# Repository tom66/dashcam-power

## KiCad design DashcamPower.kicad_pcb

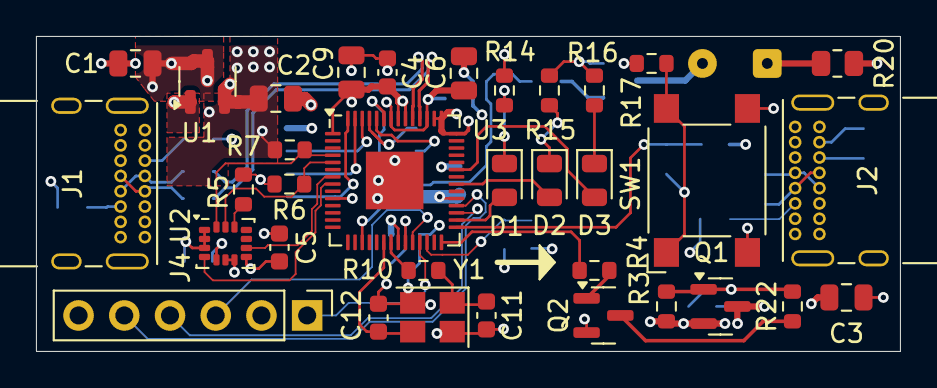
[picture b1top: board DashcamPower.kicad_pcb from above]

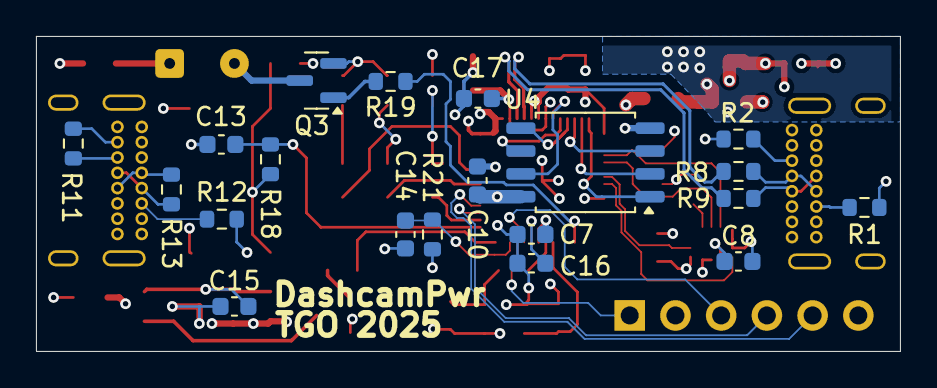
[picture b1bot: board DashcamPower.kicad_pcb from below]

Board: 6 copper layers, 48.0 x 17.5 mm, 55 parts (20 on the bottom side), 50 nets.

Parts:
C1, C3: 4.7u 25V; C_0805_2012Metric
C2, C6, C9: 1u 50V; C_0805_2012Metric
C4, C5, C7, C8, C10, C13, C14, C15, C16, C17: 100n; C_0603_1608Metric
C11, C12: 15p; C_0603_1608Metric
D1: Green 0805; LED_0805_2012Metric
D2: Red 0805; LED_0805_2012Metric
D3: Yellow 0805; LED_0805_2012Metric
J1, J2: USB_C_Receptacle_USB2.0_16P; USB_C_Receptacle_GCT_USB4085
J4: Conn_01x06; PinHeader_1x06_P2.54mm_Vertical
LS1: Speaker_Crystal; SolderWire-0.1sqmm_1x02_P3.6mm_D0.4mm_OD1mm
Q1: IRLML6402; SOT-23
Q2, Q3: MMBT5551L; SOT-23
R1, R2, R3, R4, R5, R6, R7, R11, R12, R17, R19, R21: 5.1k; R_0603_1608Metric
R8, R9: 27R; R_0603_1608Metric
R10: 1k; R_0603_1608Metric
R13: NF; R_0603_1608Metric
R14, R15, R16, R18, R22: 270R; R_0603_1608Metric
R20: 0R; R_0805_2012Metric
SW1: B3FS-1000P; SW_SPST_Omron_B3FS-100xP
U1: XC6206P332MR-G; SOT-23-3
U2: LSM6DS3; LGA-14_3x2.5mm_P0.5mm_LayoutBorder3x4y
U3: RP2040; QFN-56-1EP_7x7mm_P0.4mm_EP3.2x3.2mm
U4: W25Q128JVS; SOIC-8_5.3x5.3mm_P1.27mm
Y1: X322512MSB4SI; Crystal_SMD_Abracon_ABM8AIG-4Pin_3.2x2.5mm

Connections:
+3.3V: C2.1, C4.1, C5.1, C7.1, C8.1, C9.1, C10.1, J4.6, R5.1, R6.1, R7.1, R17.1, R21.1, U1.2 (VO), U2.5 (VDDIO), U2.8 (VDD), U3.1 (IOVDD), U3.10 (IOVDD), U3.22 (IOVDD), U3.33 (IOVDD), U3.42 (IOVDD), U3.43 (ADC_AVDD), U3.44 (VREG_IN), U3.48 (USB_VDD), U3.49 (IOVDD), U4.8 (VCC)
+5V: C1.1, J1.A4 (VBUS), J1.A9 (VBUS), J1.B4 (VBUS), J1.B9 (VBUS), Q1.2 (S), R3.1, R20.1, U1.3 (VI)
/BTN: C13.1, R18.2, U3.29 (GPIO18)
/BUZZER: R19.1, U3.17 (GPIO14)
/I2C_SCL: R6.2, U2.13 (SCL), U3.5 (GPIO3)
/I2C_SDA: R7.2, U2.14 (SDA), U3.4 (GPIO2)
/IMU_INT1: U2.4 (INT1), U3.8 (GPIO6)
/IMU_INT2: U2.9 (INT2), U3.7 (GPIO5)
/LED_G: D1.2 (A), U3.30 (GPIO19)
/LED_R: D2.2 (A), U3.35 (GPIO23)
/LED_Y: D3.2 (A), U3.37 (GPIO25)
/QSPI_CLK: U3.52 (QSPI_SCLK), U4.6 (CLK)
/QSPI_SD0: U3.53 (QSPI_SD0), U4.5 (DI/IO_{0})
/QSPI_SD1: U3.55 (QSPI_SD1), U4.2 (DO/IO_{1})
/QSPI_SD2: U3.54 (QSPI_SD2), U4.3 (~WP/IO_{2})
/QSPI_SD3: U3.51 (QSPI_SD3), U4.7 (~HOLD/~RESET/IO_{3})
/QSPI_SS: U3.56 (QSPI_SS), U4.1 (~CS)
/SWC: J4.3, U3.24 (SWCLK)
/SWD: J4.1, U3.25 (SWD)
/URX: J4.5, U3.32 (GPIO21)
/USB_D_N: J1.A7 (D-), J1.B7 (D-), R9.2
/USB_D_P: J1.A6 (D+), J1.B6 (D+), R8.1
/USB_OUT_ON: R4.1, U3.28 (GPIO17)
/USB_RES_D_N: R8.2, U3.47 (USB_DP)
/USB_RES_D_P: R9.1, U3.46 (USB_DM)
/USB_VOUT: C3.1, C15.1, J2.A4 (VBUS), J2.A9 (VBUS), J2.B4 (VBUS), J2.B9 (VBUS), Q1.3 (D), R11.1, R12.1
/UTX: J4.4, U3.31 (GPIO20)
/VCORE: C6.1, C16.1, C17.1, U3.23 (DVDD), U3.45 (VREG_VOUT), U3.50 (DVDD)
GND: C1.2, C2.2, C3.2, C4.2, C5.2, C6.2, C7.2, C8.2, C9.2, C10.2, C11.2, C12.2, C13.2, C14.2, C16.2, C17.2, J1.A1 (GND), J1.A12 (GND), J1.B1 (GND), J1.B12 (GND), J1.S1 (SHIELD), J2.A1 (GND), J2.A12 (GND), J2.B1 (GND), J2.B12 (GND), J2.S1 (SHIELD), J4.2, Q2.2 (E), Q3.2 (E), R1.2, R2.2, R14.2, R15.2, R16.2, SW1.2, U1.1 (GND), U2.1 (SDO/SA0), U2.2 (SDX), U2.3 (SCX), U2.6 (GND), U2.7 (GND), U3.57 (GND), U4.4 (GND), Y1.2, Y1.4
unnamed: C11.1, R10.1, Y1.1
unnamed: D1.1 (K), R14.1
unnamed: D2.1 (K), R15.1
unnamed: D3.1 (K), R16.1
unnamed: J1.A5 (CC1), R2.1
unnamed: J1.B5 (CC2), R1.1
unnamed: J2.A5 (CC1), R12.2
unnamed: J2.B5 (CC2), R11.2
unnamed: J2.A6 (D+), J2.B6 (D+), R13.2
unnamed: J2.A7 (D-), J2.B7 (D-), R13.1
unnamed: LS1.1, R20.2
unnamed: C15.2, Q1.1 (G), R3.2, R22.2
unnamed: Q2.1 (B), R4.2
unnamed: Q2.3 (C), R22.1
unnamed: Q3.1 (B), R19.2
unnamed: LS1.2, Q3.3 (C)
unnamed: R17.2, R18.1, SW1.1
unnamed: R5.2, U2.12 (CS)
unnamed: C14.1, R21.2, U3.26 (RUN)
unnamed: C12.1, U3.20 (XIN), Y1.3
unnamed: R10.2, U3.21 (XOUT)

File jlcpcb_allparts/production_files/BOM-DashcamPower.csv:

Comment,Designator,Footprint,LCSC,Quantity
0R,R20,R_0805_2012Metric,C17477,1
100n,"C10,C13,C14,C15,C16,C17,C4,C5,C7,C8",C_0603_1608Metric,C14663,10
15p,"C11,C12",C_0603_1608Metric,C1644,2
1k,R10,R_0603_1608Metric,C21190,1
1u 50V,"C2,C6,C9",C_0805_2012Metric,C28323,3
270R,"R14,R15,R16,R18,R22",R_0603_1608Metric,C22966,5
27R,"R8,R9",R_0603_1608Metric,C25190,2
4.7u 25V,C1,C_0805_2012Metric,C1779,1
5.1k,"R1,R11,R12,R17,R19,R2,R21,R3,R4,R5,R6,R7",R_0603_1608Metric,C23186,12
B3FS-1000P,SW1,SW_SPST_Omron_B3FS-100xP,C271750,1
Green 0805,D1,LED_0805_2012Metric,C2297,1
IRLML6402,Q1,SOT-23,C2593,1
LSM6DS3,U2,LGA-14_3x2.5mm_P0.5mm_LayoutBorder3x4y,C95230,1
MMBT5551L,"Q2,Q3",SOT-23,C2145,2
RP2040,U3,QFN-56-1EP_7x7mm_P0.4mm_EP3.2x3.2mm,C2040,1
Red 0805,D2,LED_0805_2012Metric,C84256,1
W25Q128JVS,U4,SOIC-8_5.3x5.3mm_P1.27mm,C97521,1
X322512MSB4SI,Y1,Crystal_SMD_Abracon_ABM8AIG-4Pin_3.2x2.5mm,C9002,1
XC6206P332MR-G,U1,SOT-23-3,C5446,1
Yellow 0805,D3,LED_0805_2012Metric,C2296,1

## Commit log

2025-09-19 Add gitignore file, remove backups
2025-09-19 Remove obsolete/uninteresting file
2025-09-24 Sync to server
    Changes on desktop
2025-10-01 PCB draft
2025-11-25 Ready to alter IMU
    Ready to alter IMU
2026-02-04 Update DashcamPower.kicad_prl
    sync workspaces
